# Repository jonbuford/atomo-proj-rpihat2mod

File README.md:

# atomo-proj-rpihat2mod
Raspberry Pi HAT Compatible 2 Module Designs

This design is using a KE02 44-pin microcontroller as an IO expander and stand-alone controller for a 2 IO module Atomo Controller Connector board. There are two versions, one with a 34-pin Power module and another that is only for powering by the Raspberry Pi.

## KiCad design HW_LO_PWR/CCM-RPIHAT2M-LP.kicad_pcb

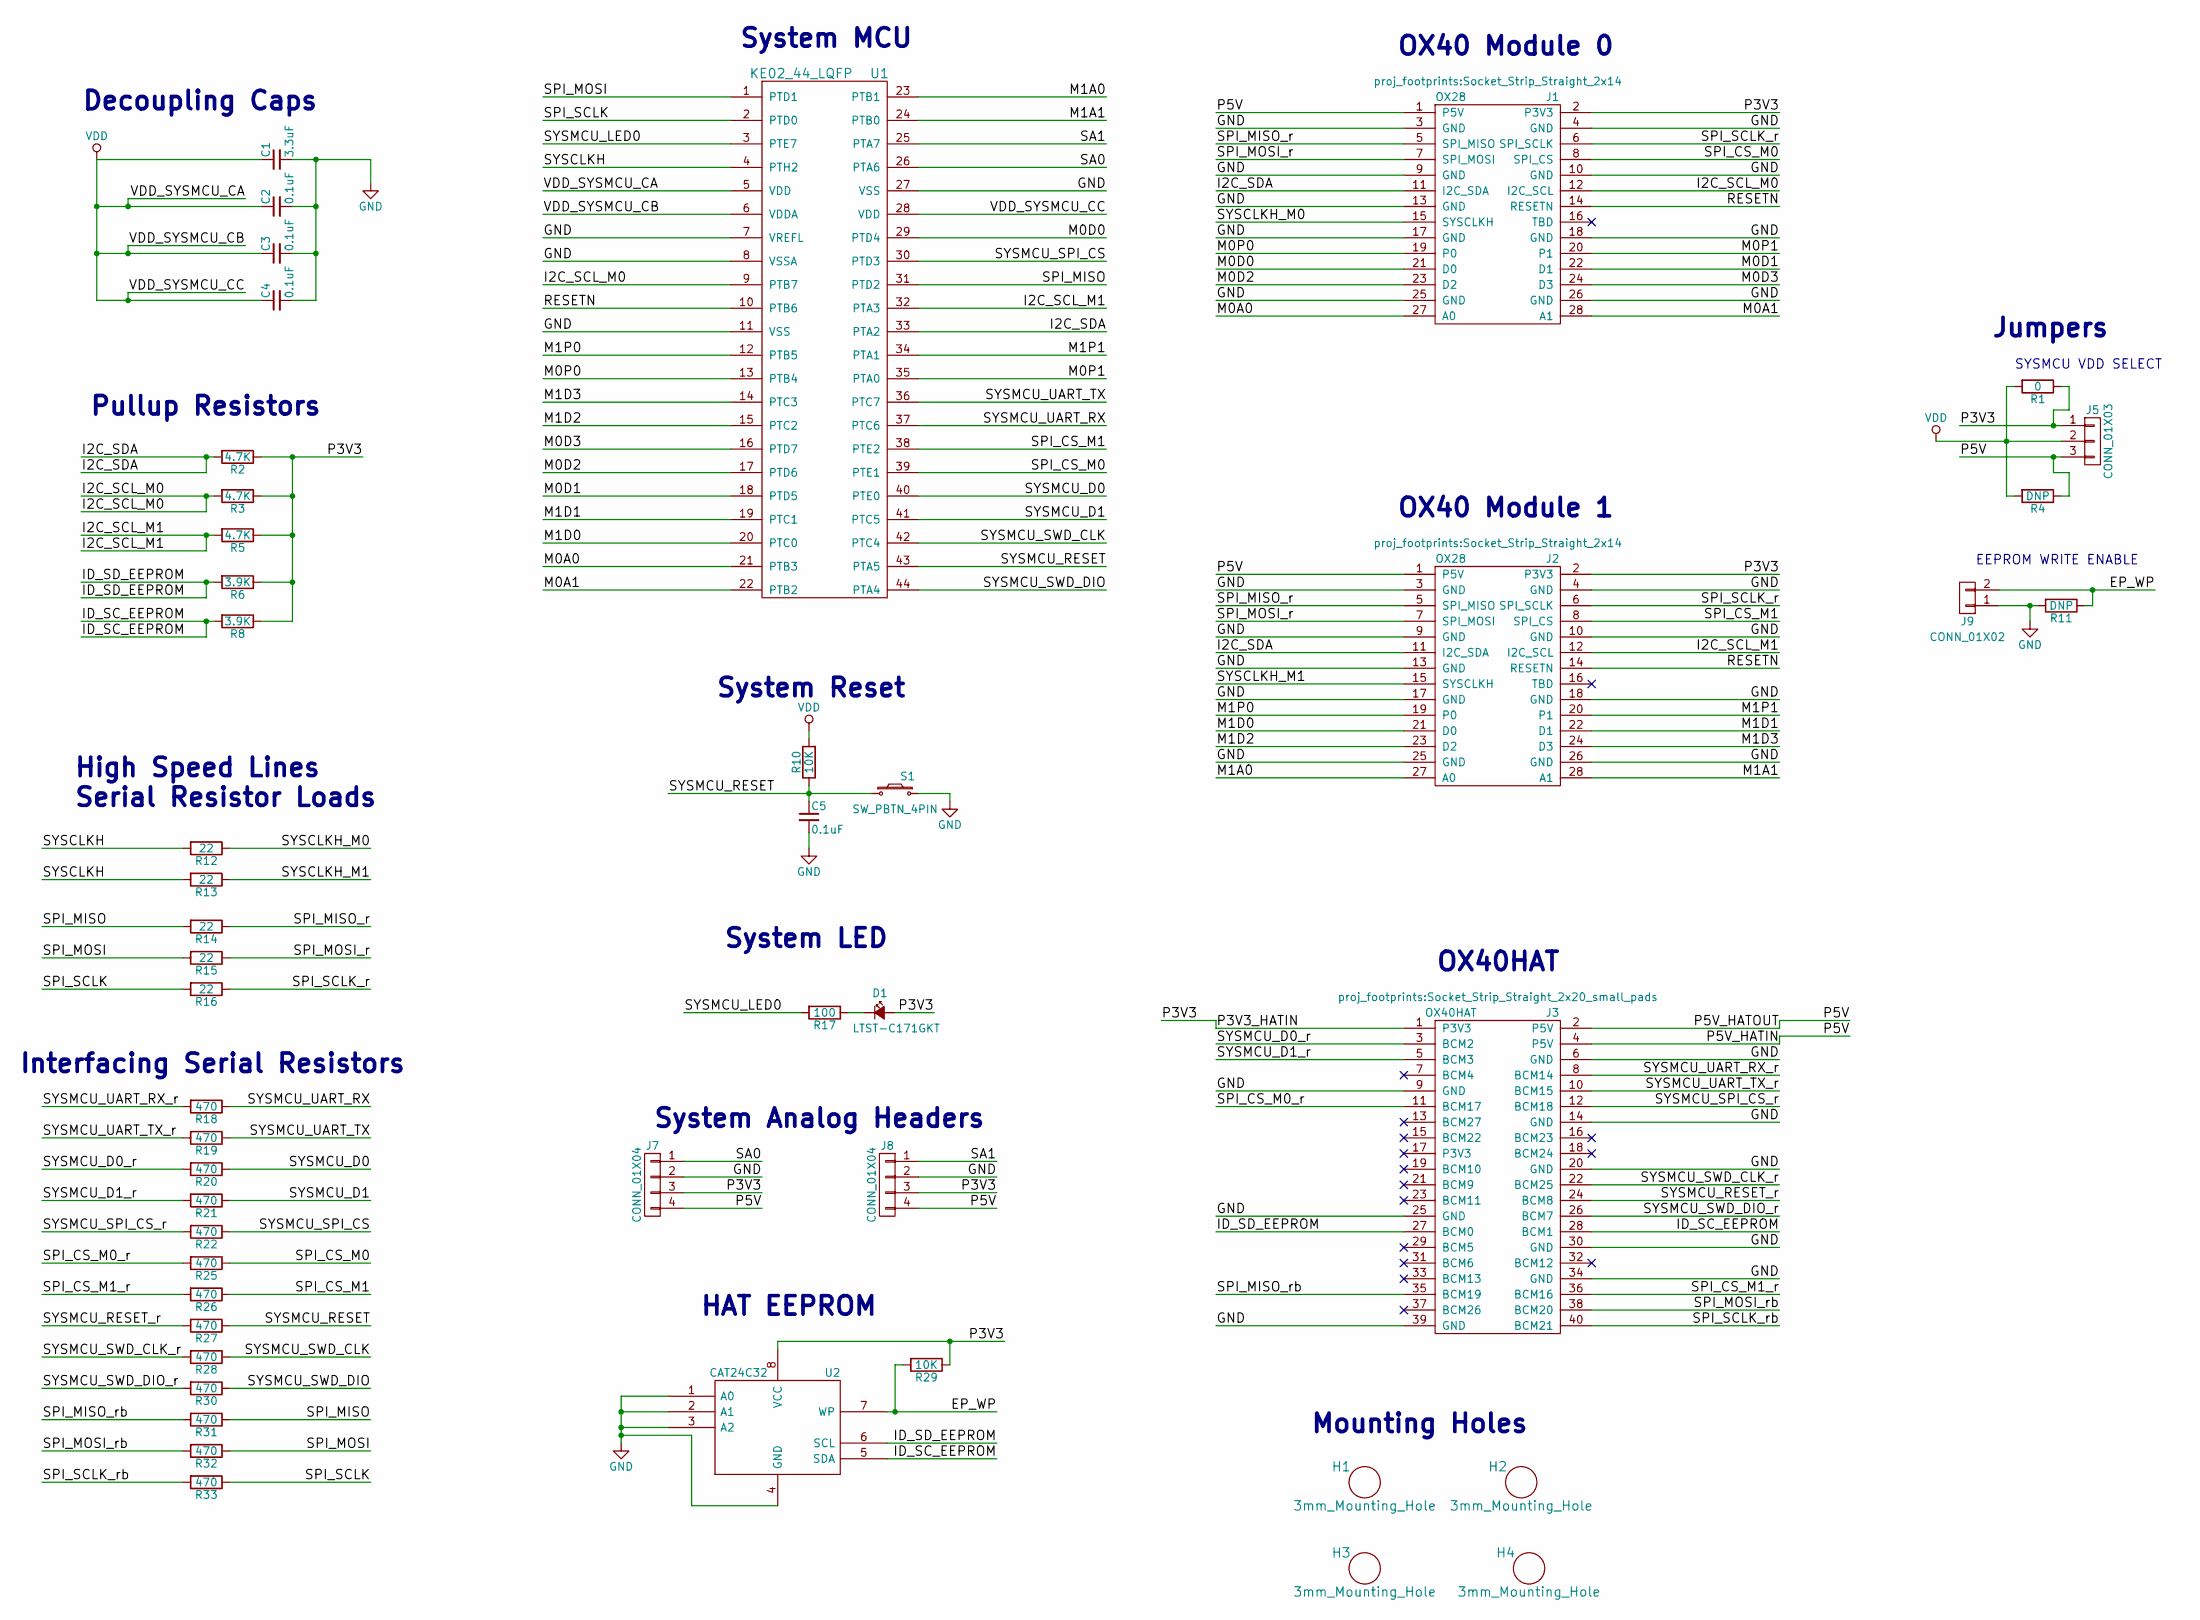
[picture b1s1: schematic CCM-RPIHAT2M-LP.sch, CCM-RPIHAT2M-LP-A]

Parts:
C1: 3.3uF; C_0603_HandSoldering; MPN GRM155R71H104ME14D
C2, C3, C4, C5: 0.1uF; C_0603_HandSoldering; MPN GRM155R71H104ME14D
D1: LTST-C171GKT; LED_0805
H1, H2, H3, H4: 3mm_Mounting_Hole; NPTH_3mm_ID
J1, J2: OX28; Socket_Strip_Straight_2x14
J3: OX40HAT; Socket_Strip_Straight_2x20_small_pads
J5: CONN_01X03; Pin_Header_Straight_1x03
J7, J8: CONN_01X04; Pin_Header_Straight_1x04
J9: CONN_01X02; Pin_Header_Straight_1x02
R1: 0; R_0805_HandSoldering; MPN RC0402JR-0722RL
R2, R3, R5: 4.7K; R_0603_HandSoldering; MPN RC0402JR-0722RL
R4, R11: DNP; R_0805_HandSoldering; MPN RC0402JR-0722RL
R6, R8: 3.9K; R_0603_HandSoldering; MPN RC0402JR-0722RL
R10, R29: 10K; R_0603_HandSoldering; MPN RC0402JR-0722RL
R12, R13, R14, R15, R16: 22; R_0603_HandSoldering; MPN RC0402JR-0722RL
R17: 100; R_0603_HandSoldering; MPN RC0402JR-0722RL
R18, R19, R20, R21, R22, R25, R26, R27, R28, R30, R31, R32, R33: 470; R_0603_HandSoldering; MPN RC0402JR-0722RL
S1: SW_PBTN_4PIN; SMT_6MM_Tact_SW
U1: KE02_44_LQFP; LQFP_44
U2: CAT24C32; SOIC-8

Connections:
/EP_WP: J9.2, R11.1, R29.2, U2.7 (WP)
/I2C_SCL_M0: J1.12 (I2C_SCL), R3.2, U1.9 (PTB7)
/I2C_SCL_M1: J2.12 (I2C_SCL), R5.2, U1.32 (PTA3)
/I2C_SDA: J1.11 (I2C_SDA), J2.11 (I2C_SDA), R2.2, U1.33 (PTA2)
/ID_SC_EEPROM: J3.28 (BCM1), R8.2, U2.5 (SDA)
/ID_SD_EEPROM: J3.27 (BCM0), R6.2, U2.6 (SCL)
/M0A0: J1.27 (A0), U1.21 (PTB3)
/M0A1: J1.28 (A1), U1.22 (PTB2)
/M0D0: J1.21 (D0), U1.29 (PTD4)
/M0D1: J1.22 (D1), U1.18 (PTD5)
/M0D2: J1.23 (D2), U1.17 (PTD6)
/M0D3: J1.24 (D3), U1.16 (PTD7)
/M0P0: J1.19 (P0), U1.13 (PTB4)
/M0P1: J1.20 (P1), U1.35 (PTA0)
/M1A0: J2.27 (A0), U1.23 (PTB1)
/M1A1: J2.28 (A1), U1.24 (PTB0)
/M1D0: J2.21 (D0), U1.20 (PTC0)
/M1D1: J2.22 (D1), U1.19 (PTC1)
/M1D2: J2.23 (D2), U1.15 (PTC2)
/M1D3: J2.24 (D3), U1.14 (PTC3)
/M1P0: J2.19 (P0), U1.12 (PTB5)
/M1P1: J2.20 (P1), U1.34 (PTA1)
/P3V3: D1.2 (A), J1.2 (P3V3), J2.2 (P3V3), J3.1 (P3V3), J5.1, J7.3, J8.3, R1.1, R2.1, R3.1, R5.1, R6.1, R8.1, R29.1, U2.8 (VCC)
/P5V: J1.1 (P5V), J2.1 (P5V), J3.2 (P5V), J3.4 (P5V), J5.3, J7.4, J8.4, R4.1
/RESETN: J1.14 (RESETN), J2.14 (RESETN), U1.10 (PTB6)
/SA0: J7.1, U1.26 (PTA6)
/SA1: J8.1, U1.25 (PTA7)
/SPI_CS_M0: J1.8 (SPI_CS), R25.1, U1.39 (PTE1)
/SPI_CS_M0_r: J3.11 (BCM17), R25.2
/SPI_CS_M1: J2.8 (SPI_CS), R26.1, U1.38 (PTE2)
/SPI_CS_M1_r: J3.36 (BCM16), R26.2
/SPI_MISO: R14.2, R31.1, U1.31 (PTD2)
/SPI_MISO_r: J1.5 (SPI_MISO), J2.5 (SPI_MISO), R14.1
/SPI_MISO_rb: J3.35 (BCM19), R31.2
/SPI_MOSI: R15.2, R32.1, U1.1 (PTD1)
/SPI_MOSI_r: J1.7 (SPI_MOSI), J2.7 (SPI_MOSI), R15.1
/SPI_MOSI_rb: J3.38 (BCM20), R32.2
/SPI_SCLK: R16.2, R33.1, U1.2 (PTD0)
/SPI_SCLK_r: J1.6 (SPI_SCLK), J2.6 (SPI_SCLK), R16.1
/SPI_SCLK_rb: J3.40 (BCM21), R33.2
/SYSCLKH: R12.2, R13.2, U1.4 (PTH2)
/SYSCLKH_M0: J1.15 (SYSCLKH), R12.1
/SYSCLKH_M1: J2.15 (SYSCLKH), R13.1
/SYSMCU_D0: R20.1, U1.40 (PTE0)
/SYSMCU_D0_r: J3.3 (BCM2), R20.2
/SYSMCU_D1: R21.1, U1.41 (PTC5)
/SYSMCU_D1_r: J3.5 (BCM3), R21.2
/SYSMCU_LED0: R17.2, U1.3 (PTE7)
/SYSMCU_RESET: C5.1, R10.1, R27.1, S1.1, S1.2, U1.43 (PTA5)
/SYSMCU_RESET_r: J3.24 (BCM8), R27.2
/SYSMCU_SPI_CS: R22.1, U1.30 (PTD3)
/SYSMCU_SPI_CS_r: J3.12 (BCM18), R22.2
/SYSMCU_SWD_CLK: R28.1, U1.42 (PTC4)
/SYSMCU_SWD_CLK_r: J3.22 (BCM25), R28.2
/SYSMCU_SWD_DIO: R30.1, U1.44 (PTA4)
/SYSMCU_SWD_DIO_r: J3.26 (BCM7), R30.2
/SYSMCU_UART_RX: R18.1, U1.37 (PTC6)
/SYSMCU_UART_RX_r: J3.8 (BCM14), R18.2
/SYSMCU_UART_TX: R19.1, U1.36 (PTC7)
/SYSMCU_UART_TX_r: J3.10 (BCM15), R19.2
GND: C1.2, C2.2, C3.2, C4.2, C5.2, J1.3 (GND), J1.4 (GND), J1.9 (GND), J1.10 (GND), J1.13 (GND), J1.17 (GND), J1.18 (GND), J1.25 (GND), J1.26 (GND), J2.3 (GND), J2.4 (GND), J2.9 (GND), J2.10 (GND), J2.13 (GND), J2.17 (GND), J2.18 (GND), J2.25 (GND), J2.26 (GND), J3.6 (GND), J3.9 (GND), J3.14 (GND), J3.20 (GND), J3.25 (GND), J3.30 (GND), J3.34 (GND), J3.39 (GND), J7.2, J8.2, J9.1, R11.2, S1.3, S1.4, U1.7 (VREFL), U1.8 (VSSA), U1.11 (VSS), U1.27 (VSS), U2.1 (A0), U2.2 (A1), U2.3 (A2), U2.4 (GND)
unnamed: D1.1 (K), R17.1
VDD: C1.1, C2.1, C3.1, C4.1, J5.2, R1.2, R4.2, R10.2, U1.5 (VDD), U1.6 (VDDA), U1.28 (VDD)

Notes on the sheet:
OX40 Module 1
OX40 Module 0
Decoupling Caps
Jumpers
SYSMCU VDD SELECT
EEPROM WRITE ENABLE
Pullup Resistors
HAT EEPROM
System Analog Headers
System LED
System Reset
Interfacing Serial Resistors
High Speed Lines Serial Resistor Loads
Mounting Holes
OX40HAT
System MCU

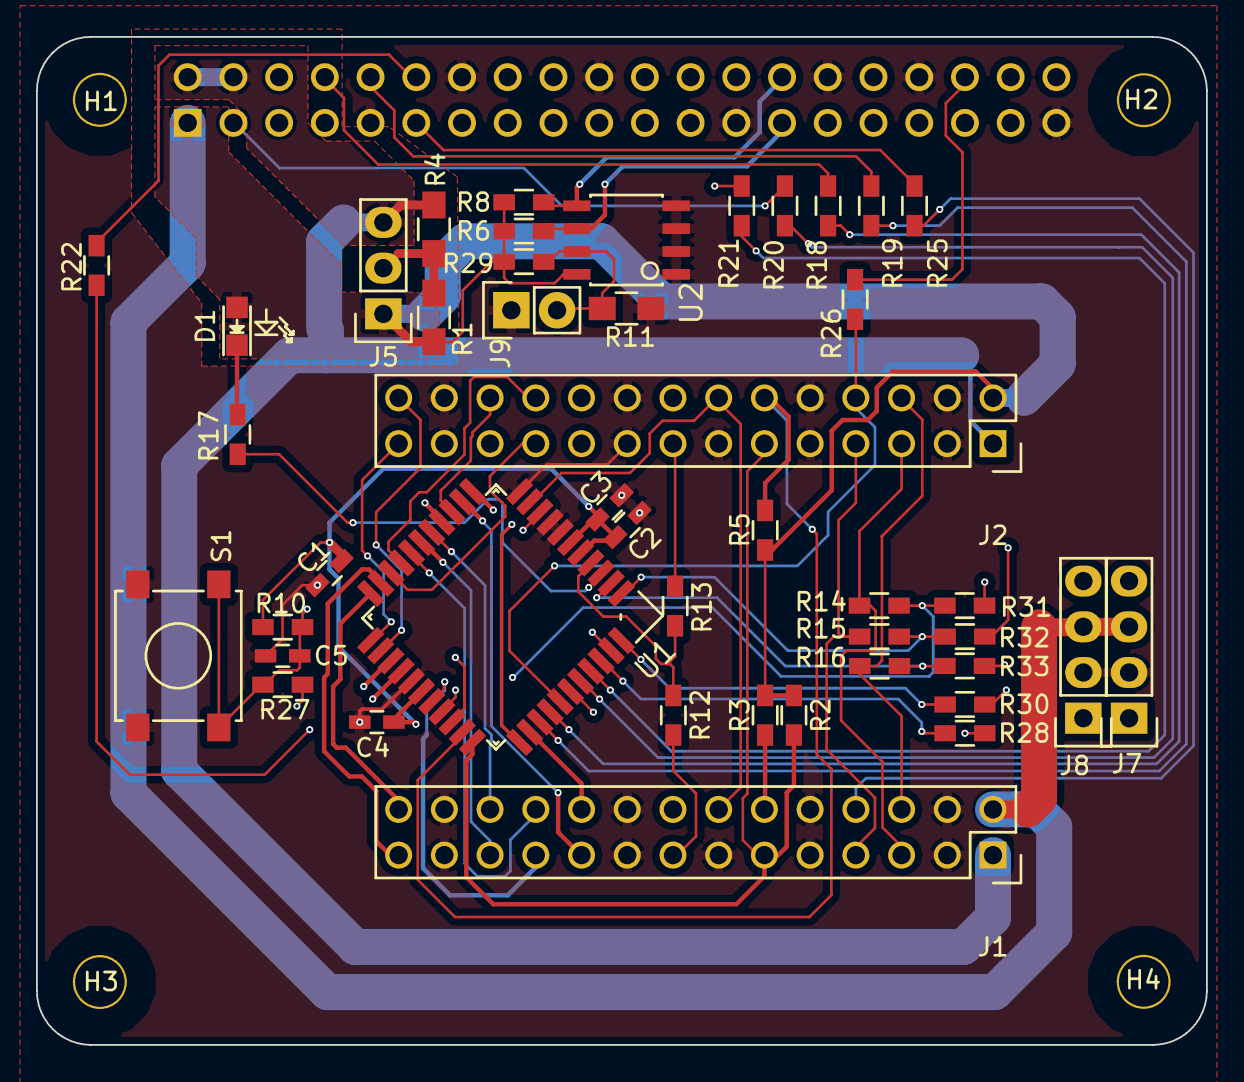
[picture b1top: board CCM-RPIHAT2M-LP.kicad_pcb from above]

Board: 4 copper layers, 65.0 x 56.0 mm, 49 parts (1 on the bottom side), 63 nets.

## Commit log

2017-04-05 :space_invader: Added .gitattributes & .gitignore files
2017-04-05 Initial Commit of KiCAD Files
    This includes both designs for 2 module HAT boards. It doesn't have a
    copy of the libraries used, and some components need 3D models created,
    but this would still be usable for designing a new version as it is.
    This design includes a 44-pin version of the KE02 MCU as the IO expander
    and stand-alone controller on the connector board. See
    http://atomosys.com for more details.
2017-04-05 Updating the Readme
